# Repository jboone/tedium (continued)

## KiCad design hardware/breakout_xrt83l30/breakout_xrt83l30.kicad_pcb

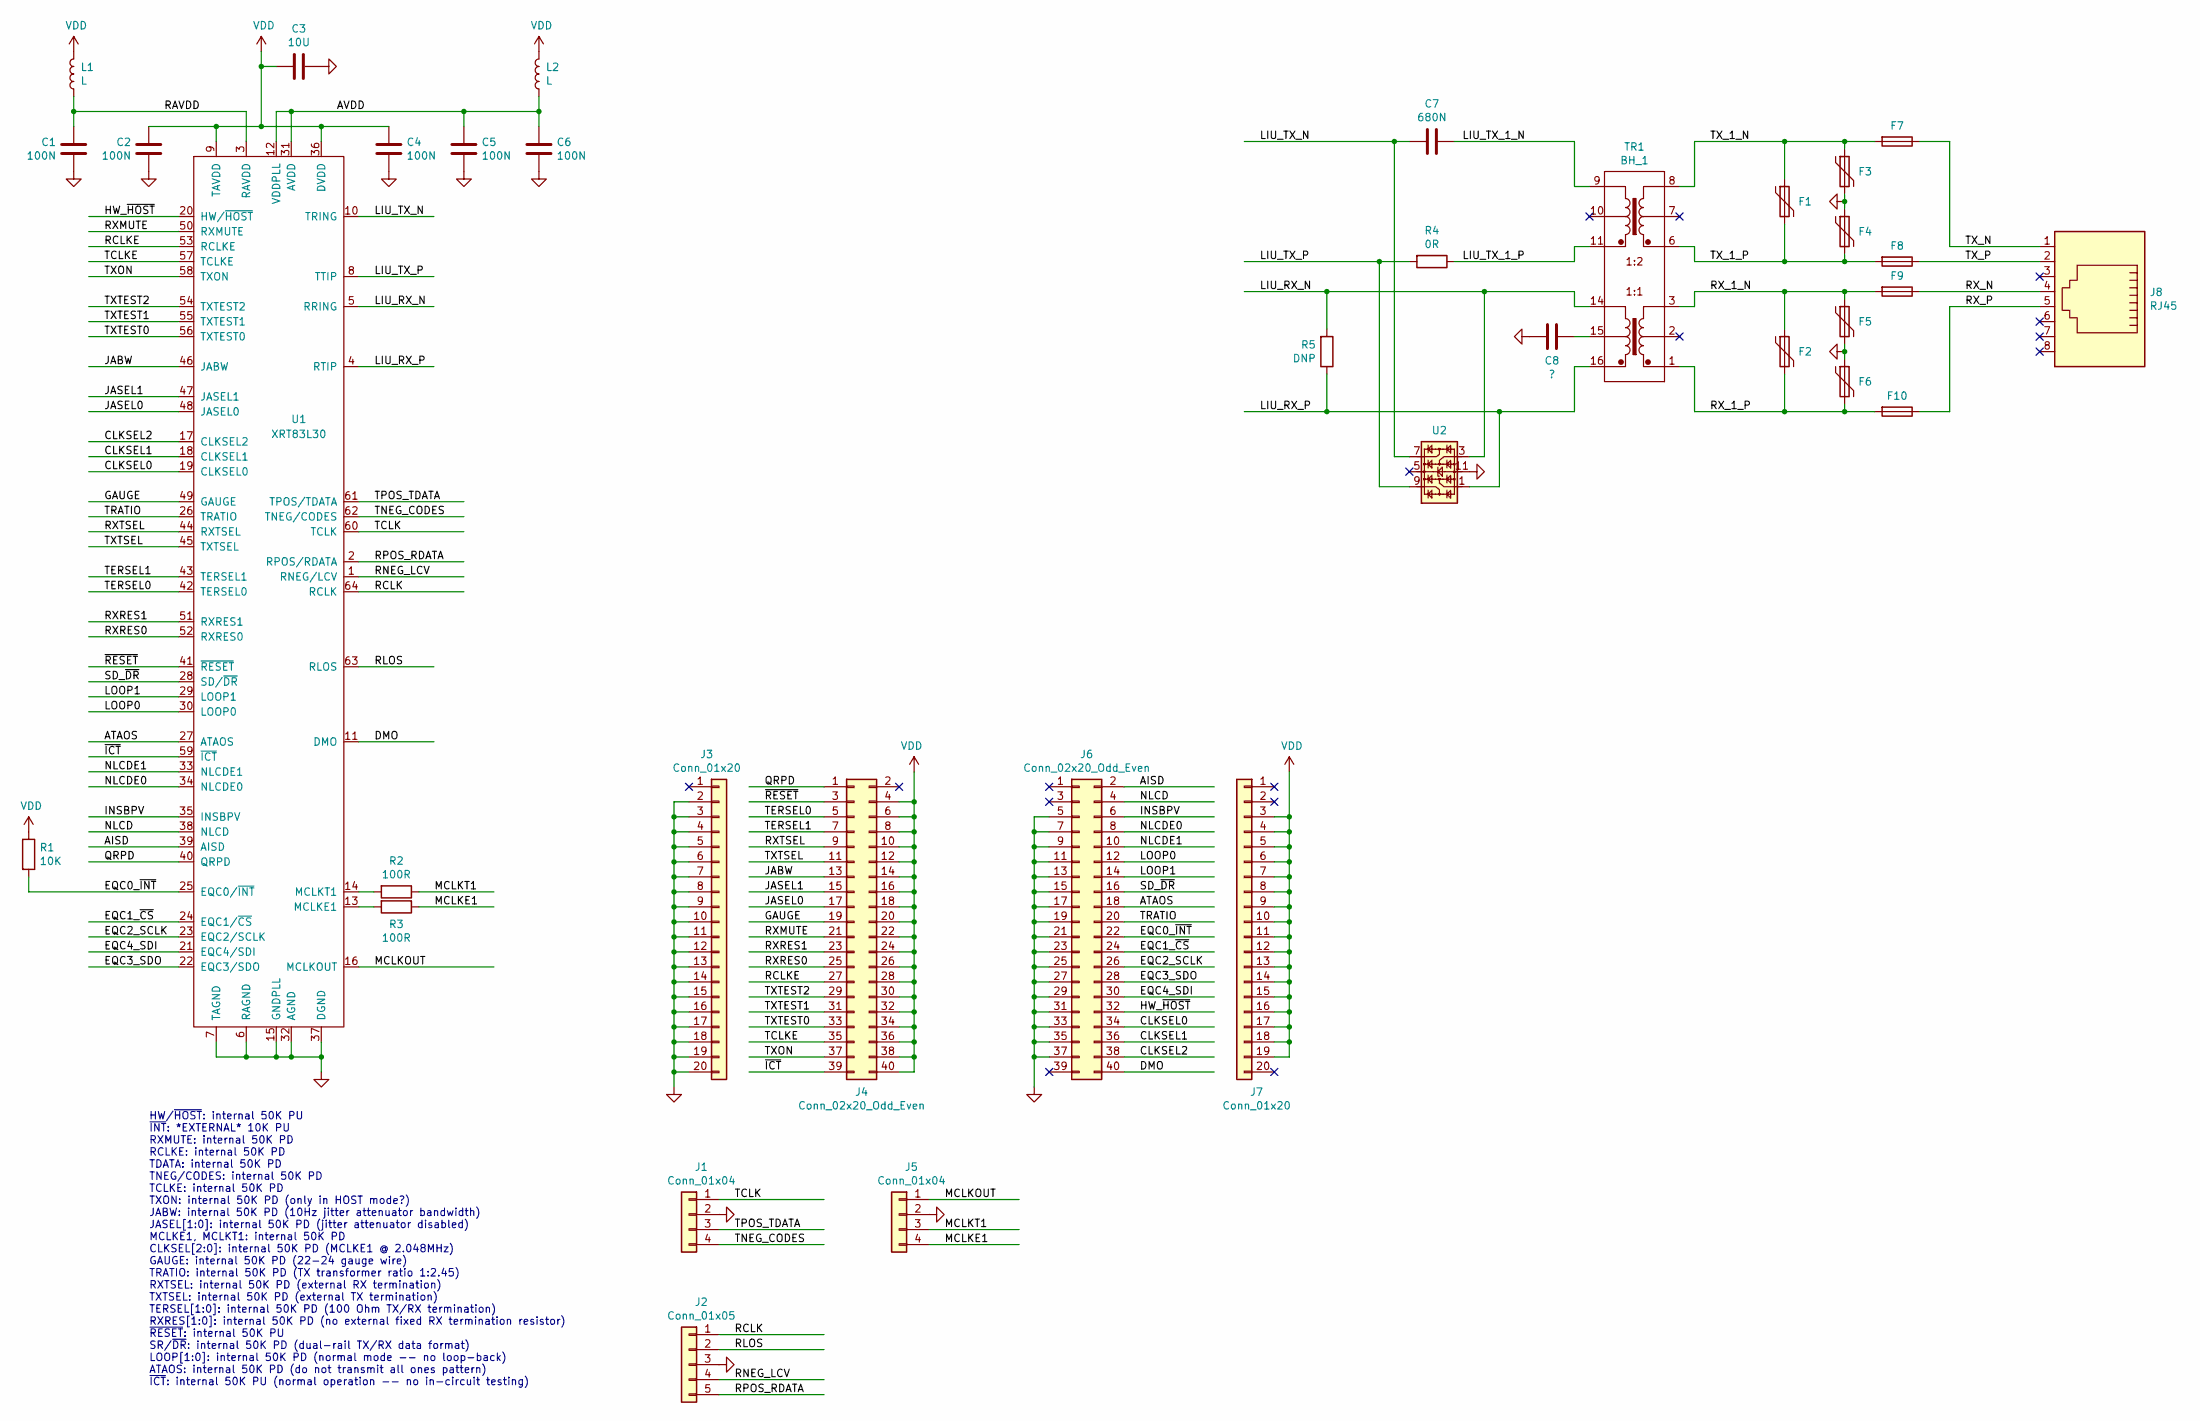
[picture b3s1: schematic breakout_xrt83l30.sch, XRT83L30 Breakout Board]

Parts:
C1, C2, C4, C5, C6: 100N; IPC_CAPC100X50X55L25N
C3: 10U; IPC_CAPC200X125X135L45N
C7: 680N; IPC_CAPC100X50X55L25N
C8: ?; IPC_CAPC200X125X135L45N
F1, F2: Polyfuse; DO-214AA; Part ‎P0080SCMCLRP‎
F3, F4, F5, F6: Polyfuse; DO-214AA; Part ‎P1800SCMCLRP‎
F7, F8, F9, F10: Fuse; 461; Part 04611.25ER
J1, J5: Conn_01x04; PinHeader_1x04_P2.54mm_Vertical
J2: Conn_01x05; PinHeader_1x05_P2.54mm_Vertical
J3, J7: Conn_01x20; PinHeader_1x20_P2.54mm_Vertical
J4, J6: Conn_02x20_Odd_Even; PinHeader_2x20_P2.54mm_Vertical
J8: RJ45; AMPHENOL_RJHSE5080
L1, L2: L; IPC_INDC160X80X100L30N
R1: 10K; IPC_RESC160X80X55L25N
R2, R3: 100R; IPC_RESC160X80X55L25N
R4: 0R; IPC_RESC100X50X40L25N
R5: DNP; IPC_RESC100X50X40L25N
TR1: BH_1; BH; Part T1094NL
U1: XRT83L30; IPC_QFP64P50_1200X1200X160L60X20N
U2: RClamp3304NA; IPC_SON11P50_260X260X65L35X25T215X126N; Part RClamp3304NA

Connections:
/AISD: J6.2, U1.39 (AISD)
/ATAOS: J6.18, U1.27 (ATAOS)
/AVDD: C5.2, C6.2, L2.1, U1.12 (VDDPLL), U1.31 (AVDD)
/CLKSEL0: J6.34, U1.19 (CLKSEL0)
/CLKSEL1: J6.36, U1.18 (CLKSEL1)
/CLKSEL2: J6.38, U1.17 (CLKSEL2)
/DMO: J6.40, U1.11 (DMO)
/EQC0_~INT: J6.22, R1.2, U1.25 (EQC0/~INT)
/EQC1_~CS: J6.24, U1.24 (EQC1/~CS)
/EQC2_SCLK: J6.26, U1.23 (EQC2/SCLK)
/EQC3_SDO: J6.28, U1.22 (EQC3/SDO)
/EQC4_SDI: J6.30, U1.21 (EQC4/SDI)
/GAUGE: J4.19, U1.49 (GAUGE)
/HW_~HOST: J6.32, U1.20 (HW/~HOST)
/INSBPV: J6.6, U1.35 (INSBPV)
/JABW: J4.13, U1.46 (JABW)
/JASEL0: J4.17, U1.48 (JASEL0)
/JASEL1: J4.15, U1.47 (JASEL1)
/LIU_RX_N: R5.2, TR1.14, U1.5 (RRING), U2.3
/LIU_RX_P: R5.1, TR1.16, U1.4 (RTIP), U2.1
/LIU_TX_1_N: C7.1, TR1.9
/LIU_TX_1_P: R4.1, TR1.11
/LIU_TX_N: C7.2, U1.10 (TRING), U2.7
/LIU_TX_P: R4.2, U1.8 (TTIP), U2.9
/LOOP0: J6.12, U1.30 (LOOP0)
/LOOP1: J6.14, U1.29 (LOOP1)
/MCLKE1: J5.4, R3.1
/MCLKOUT: J5.1, U1.16 (MCLKOUT)
/MCLKT1: J5.3, R2.1
/NLCD: J6.4, U1.38 (NLCD)
/NLCDE0: J6.8, U1.34 (NLCDE0)
/NLCDE1: J6.10, U1.33 (NLCDE1)
/QRPD: J4.1, U1.40 (QRPD)
/RAVDD: C1.2, L1.1, U1.3 (RAVDD)
/RCLK: J2.1, U1.64 (RCLK)
/RCLKE: J4.27, U1.53 (RCLKE)
/RLOS: J2.2, U1.63 (RLOS)
/RNEG_LCV: J2.4, U1.1 (RNEG/LCV)
/RPOS_RDATA: J2.5, U1.2 (RPOS/RDATA)
/RXMUTE: J4.21, U1.50 (RXMUTE)
/RXRES0: J4.25, U1.52 (RXRES0)
/RXRES1: J4.23, U1.51 (RXRES1)
/RXTSEL: J4.9, U1.44 (RXTSEL)
/RX_1_N: F2.1, F5.1, F9.2, TR1.3
/RX_1_P: F2.2, F6.2, F10.2, TR1.1
/RX_N: F9.1, J8.4
/RX_P: F10.1, J8.5
/SD_~DR: J6.16, U1.28 (SD/~DR)
/TCLK: J1.1, U1.60 (TCLK)
/TCLKE: J4.35, U1.57 (TCLKE)
/TERSEL0: J4.5, U1.42 (TERSEL0)
/TERSEL1: J4.7, U1.43 (TERSEL1)
/TNEG_CODES: J1.4, U1.62 (TNEG/CODES)
/TPOS_TDATA: J1.3, U1.61 (TPOS/TDATA)
/TRATIO: J6.20, U1.26 (TRATIO)
/TXON: J4.37, U1.58 (TXON)
/TXTEST0: J4.33, U1.56 (TXTEST0)
/TXTEST1: J4.31, U1.55 (TXTEST1)
/TXTEST2: J4.29, U1.54 (TXTEST2)
/TXTSEL: J4.11, U1.45 (TXTSEL)
/TX_1_N: F1.1, F3.1, F7.2, TR1.8
/TX_1_P: F1.2, F4.2, F8.2, TR1.6
/TX_N: F7.1, J8.1
/TX_P: F8.1, J8.2
/~ICT: J4.39, U1.59 (~ICT)
/~RESET: J4.3, U1.41 (~RESET)
GND: C1.1, C2.1, C3.2, C4.1, C5.1, C6.1, C8.2, F3.2, F4.1, F5.2, F6.1, J1.2, J2.3, J3.2, J3.3, J3.4, J3.5, J3.6, J3.7, J3.8, J3.9, J3.10, J3.11, J3.12, J3.13, J3.14, J3.15, J3.16, J3.17, J3.18, J3.19, J3.20, J5.2, J6.5, J6.7, J6.9, J6.11, J6.13, J6.15, J6.17, J6.19, J6.21, J6.23, J6.25, J6.27, J6.29, J6.31, J6.33, J6.35, J6.37, U1.6 (RAGND), U1.7 (TAGND), U1.15 (GNDPLL), U1.32 (AGND), U1.37 (DGND), U2.11
unnamed: C8.1, TR1.15
unnamed: R2.2, U1.14 (MCLKT1)
unnamed: R3.2, U1.13 (MCLKE1)
VDD: C2.2, C3.1, C4.2, J4.4, J4.6, J4.8, J4.10, J4.12, J4.14, J4.16, J4.18, J4.20, J4.22, J4.24, J4.26, J4.28, J4.30, J4.32, J4.34, J4.36, J4.38, J4.40, J7.3, J7.4, J7.5, J7.6, J7.7, J7.8, J7.9, J7.10, J7.11, J7.12, J7.13, J7.14, J7.15, J7.16, J7.17, J7.18, J7.19, L1.2, L2.2, R1.1, U1.9 (TAVDD), U1.36 (DVDD)

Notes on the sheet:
HW/~HOST~: internal 50K PU ~INT~: *EXTERNAL* 10K PU RXMUTE: internal 50K PD RCLKE: internal 50K PD TDATA: internal 50K PD TNEG/CODES: internal 50K PD TCLKE: internal 50K PD TXON: internal 50K PD (only in HOST mode?) JABW: internal 50K PD (10Hz jitter attenuator bandwidth) JASEL[1:0]: internal 50K P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

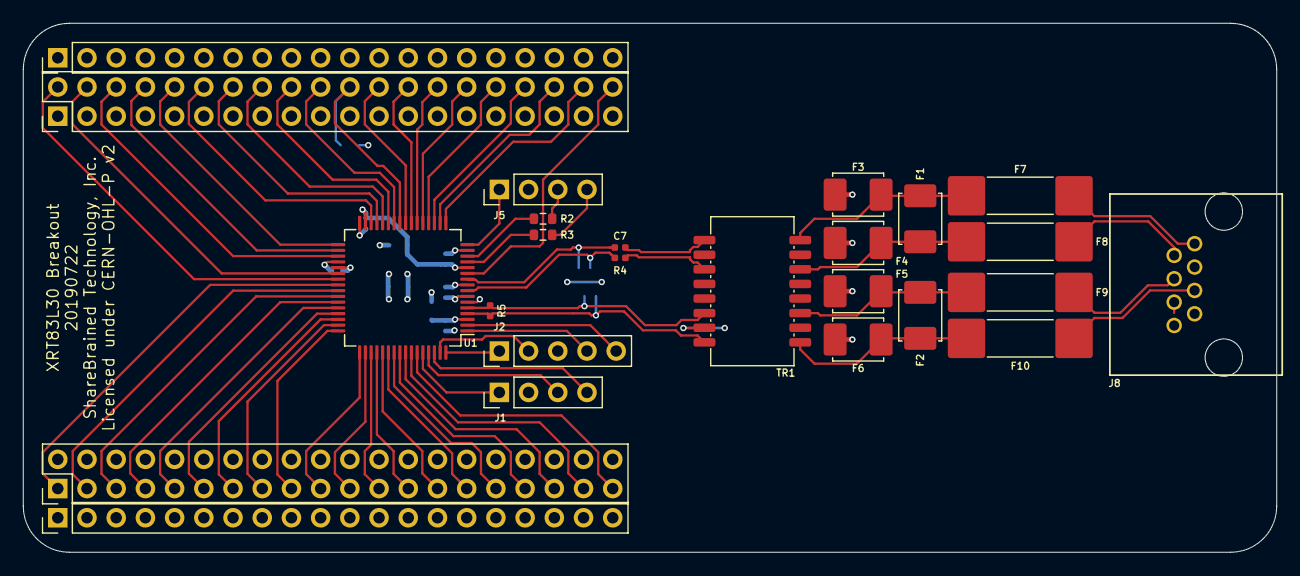
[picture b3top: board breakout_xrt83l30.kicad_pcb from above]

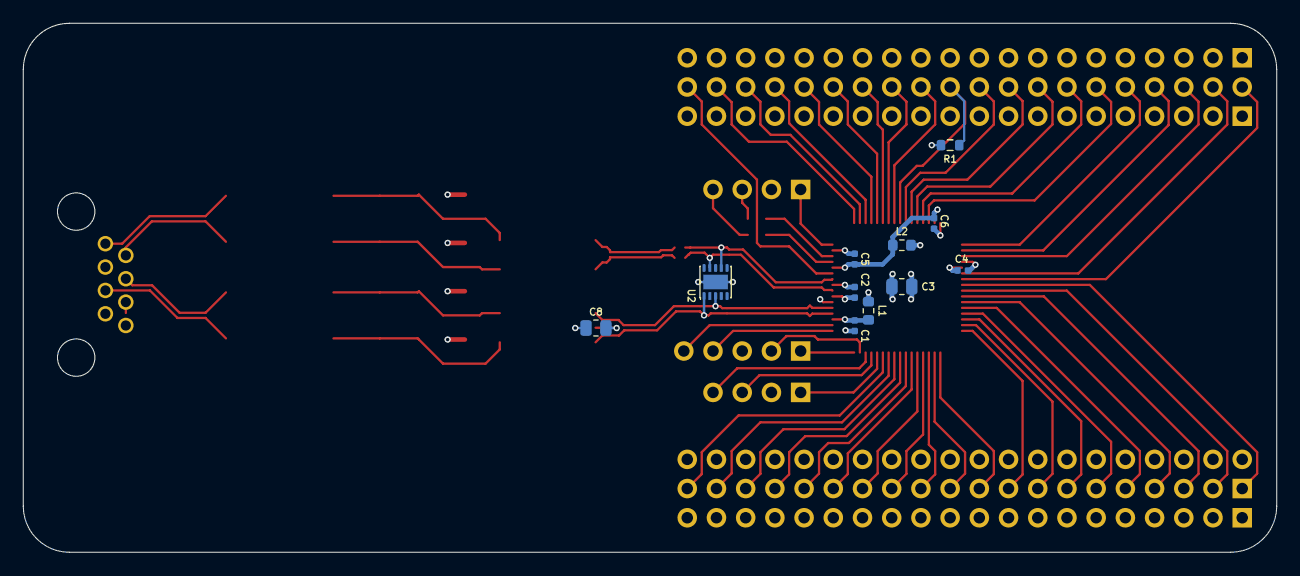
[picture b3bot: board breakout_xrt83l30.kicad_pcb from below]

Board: 4 copper layers, 109.0 x 46.0 mm, 36 parts (11 on the bottom side), 71 nets.

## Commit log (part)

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2019-07-23 Hopefully complete XRT83L30 breakout design.
2019-08-16 Add license, for source code at least.
2019-08-16 Quick dumb Rust test to parse a file of ESF-structured bits. Not terribly useful yet...
2019-08-16 Rust: Save file of 24 channels of raw audio data.
2020-05-29 Relocate XRT83L30 breakout schematic/PCB files.
2020-05-30 Update/apply XRT83L30 breakout schematic license and release dates.
2020-05-30 Add XRT83L30 breakout schematic for reference by non-KiCAD people.
2020-05-30 Add XRT83L30 configuration and bring-up doc.
2020-05-30 Add license for hardware: CERN OHL v2 Permissive
2020-05-30 Update name of project in README.
2020-05-30 Update license info in README.
2020-05-30 Update XRT83L30 breakout schematic -cache.lib because... why?
2020-05-30 Add Tedium X8 (8-span framer/LIU + FPGA + USB + power) schematic/PCB design.
2020-05-30 Remove redundant cached library for XRT83L30 breakout board.
2021-09-01 HW: Tedium X8: Misc schematic comments.
2021-09-01 HW: Tedium X8: Add KiCAD 5.99 project file.
2021-09-01 Rework Rust framer to support ESF.
2021-09-01 Tedium X8 PHY initial design.
    Weak, but it does the job.
2021-09-01 HW: Tedium X8: Add .kicad_prl file
    I guess they separated out UI state from the rest of the project file? Maybe this doesn't belong in the repo?
2021-09-01 HW: Tedium X8: Remove old-KiCAD .pro file.
2021-09-01 Add my KiCAD repo as a submodule.
    I don't like this approach very much, but not sure what's better...
2021-09-01 HW: Tedium X8: Update symbols, footprints, KiCAD to 5.99-now.
2021-09-01 Relicense using BSD 3-Clause.
    Apache and MIT seems complex. Yeah, Rust does it that way. But that doesn't mean I have to.
2021-09-01 Add LUNA-based gateware and tooling/tools.
2021-09-02 Update license on old Rust framer code.
2021-09-19 Reorganize USB endpoint constants
    Borrowing structure from a USB audio device.
2021-09-19 More notes on setup and debugging.
2021-09-19 Further USB descriptor tweaking.
    Set self-powered, 100mA current, remove serial number, add device version number.
2022-06-21 New Rust tedium-tool.
2022-06-21 Remove old Rust framer code.
2022-06-21 Isochronous USB tests in C.
2022-06-21 Some Python ESF frame dumper I cobbled together...
2022-06-21 Clean up Python module imports and directory structure.
2022-06-21 Push forked dependencies to GitHub, point pyproject at them.
2022-06-21 Update top-level README, reflecting significant changes in project.
2022-06-21 Whoops, enable TX side of FPGA framer.
2022-06-21 Fix endpoint numbering on host side.
2022-06-21 Add TX-side structures, and logic to set OUT packet sizes.
2022-06-21 Remove extraneous comment, extra whitespace.
2022-06-22 Remove old, commented-out dependencies.
2022-06-22 Remove message channel, track USB/frame sequences, move frames through ringbuf.
2022-06-22 Drain frame ringbuf as fast as possible.
2022-06-22 Naively pass received frame count to transmitted frame.
    Eventually, I intend for the FPGA to use the frame count as a presentation timestamp, and the host will advance the received count by a constant latency (number of frames). This should make latency m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
2022-06-22 Add simple (and not-so-great) closed-loop TX FIFO management.
2022-06-22 Rename some USB transaction/packet count constants.
2022-06-22 Separate IN/OUT handlers from callback traits.
    First step of larger refactoring.
2022-06-22 Rename internal frames ringbuf producer/consumer.
2022-06-22 Extract the RX packet processing into separate entities.
    Separation of concerns, yay! Keep the gnarly and unsafe USB code contained!
2022-06-22 First pass: collect and report framer statistics.
2022-06-22 Separate periodic and cumulative framer statistics.
2022-06-22 Remove a bunch of old code.
2022-06-22 Loop (poorly-named) processor into audio loop.
2022-06-22 Rename the thing that does the audio processing.
2022-06-22 Quick cut at altering the audio/switch patching at runtime.
2022-06-22 Use thread::Builder to give threads names for better debugging.
2022-06-23 Relocate Microprocessor interface test to tests/hdl.
2022-06-23 Remove some dead/commented code
2022-06-23 Move USB<->microprocessor handler into separate file.
2022-06-23 Reintroduce USB interrupt endpoint for framer INT#.
2022-06-23 Remove more dead code.
2022-06-23 Remove crusty old USB isochronous test program.
2022-06-23 Move USB config info into module, fix interrupt endpoint number.
2022-06-24 Add USB interrupt IN endpoint simulation.
2022-06-24 Move framer->USB interrupt logic out of endpoint code.
2022-06-24 "Fix" framer->USB interrupts, at least temporariliy.
    TODO: This method certainly transmits far more interrupts than necessary, and likely wastes some small (likely insignificant) amount of the host's time. I suppose it offends me aesthetically more tha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
2022-06-24 Missed committing sneaky comment about RTKit thread priority.
2022-06-25 Add common reset signal for PLLs, currently held at 0/false.
2022-06-25 Remove clkref domain.
2022-06-25 Add FTDI-attached UARTResource.
2022-06-25 Fix platform default clock frequencies.
2022-06-25 Clean up clock signal resets.
2022-06-25 Move MCLKIN assignment to clock domain generator.
2022-06-25 Clean up whitespace, remove commented code.
2022-06-26 Cargo-culting little tweak to ensure reference clock is an input.
2022-06-26 Revert "Simplify and speed up microprocessor interface."
    This reverts commit f15058377d9bab2b0ec8e4d6040b9b5df1753b87.
2022-06-26 Add MicroprocessorInterface `done` strobe signal.
2022-06-28 Extract microprocessor bus wait-state into constant.
2022-06-28 Add firmware Rust code and semi-generalized framer peripheral crate.
2022-06-28 Add typing to top module `platform` for code completion.
2022-06-28 Change building of top-level module to support SoC.
2022-06-28 Whoops, add platform to usb_framer elaboration function.
2022-06-28 Introduce SoC, move framer hardware reset control to SoC CSR.
2022-06-28 Half-heartedly update READMEs.
2022-06-28 openocd: Remove redundant selection of JTAG transport mode.
2022-06-28 Break nascent firmware into several source files.
2022-06-28 Note about how to reload the FPGA without rebuilding the bitstream.
2022-06-28 Add some useful bits to the dumb UART.
    Trying not to be embarrassed.
2022-06-28 firmware: basic interrupt checking.
2022-06-28 Bump linker RAM size to 16K to match earlier gateware change.
2022-06-28 Enable debouncing of RBS state on all timeslots.
2022-06-28 Add a couple of firmware start-up progress messages.
2022-06-28 Allow comparisons of RSAR registers.
2022-06-28 Quick and dirty monitoring of per-timeslot RBS state.
2022-06-29 More thorough clearing of HDLC/SS7-related interrupts.
2022-06-29 Firmware: Report interrupt status to host over USB IN endpoint.
2022-06-29 Typo/comment clean-up.
2022-06-29 firmware: Accept USB OUT transfers.
    They're just being printed via the UART right now, but we'll do something more interesting with them soon...
2022-06-29 Prevent firmware from being built at workspace level.
    Doing so would ignore the firmware project's .cargo configuration, which is critical for getting the correct binary.
2022-06-29 firmware: Optimize for size.
2022-06-29 Remove a couple of bits of commented-out code.
2022-06-29 firmware: Break USB, Peripheral into separate files.
2022-06-29 Remove init code from host side, now the firmware does it.
2022-06-29 firmware: Change resync feature to have trigger boolean.
    Eventually, the host will be able to trigger a resync.
2022-06-29 Move IsochronousTransfer to usb module.
    It'll get generalized soon...
2022-06-29 Rename USB transfer callback.
2022-06-29 Generalize async USB transfer handler, improve framer interrupt thread..
2022-06-29 firmware: Only arm interrupt IN when there's data in the FIFO.
    This prevents a ton of zero-length packets (ZLPs) being sent to the host and waking it up unnecessarily.
2022-06-29 Pipe framer interrupt data through to receiver thread.
2022-06-29 Oh look, more host code that was moved to the SoC.
2022-06-29 firmware: Restore unhandled BISR events and comments for each event type.
2022-06-29 firmware: Send correct RLCISRx registers for LBCODE, fix PAC crate.
2022-06-29 firmware: Send entire RDLBC register, not just byte count.
2022-06-29 Firmware: rename timeslot RBS nibbles for clarity.
2022-06-29 Firmware: Always report HDLC length, read bytes, if DLSR is not zero.
2022-06-29 Firmware: Report SS7SRx.
2022-06-29 Parse and pretty-print framer interrupt messages.
    This needs to be refactored into separate parsing and presentation, obviously...
2022-06-30 Proper parsing and displaying of framer interrupts.
2022-06-30 Move framer register dump functions, remove commented code.
2022-06-30 Put a copy of USB descriptor constants in firmware.
2022-06-30 Add some missing USB descriptor constants.
2022-06-30 Separate host command parsing from processing.
2022-06-30 Change Python host command test to do a register read.
2022-06-30 Move OUT endpoint check outside of command parser.
2022-07-01 Remove `owner` register from USB OUT endpoint.
2022-07-01 Do some SoC USB variable renaming.
2022-07-01 Firmware: Move USB IN interrupt checking to later to not starve host requests.
2022-07-01 Remove commented code.
2022-07-01 Add USB IN endpoint for host commands.
2022-07-01 Firmware: USB OUT: check `enable` first for endpoint transaction completion.
2022-07-01 Firmware: USB IN: Add `is_stalled` function.
2022-07-01 Test: Host Request: separate read and write exceptions, run as fast as possible.
2022-07-01 Test: Make host command test quieter, faster, for max damage.
2022-07-01 Firmware: Tighten up RegisterRead, monitor for unexpected USB IN state.
2022-07-01 Firmware: Add register-write host command.
2022-07-01 Test: Rewrite host command test, more tidy, with multiple tests.
2022-07-01 Firmware: Add UART test code.
    I might never use it again, but who knows...
2022-07-01 Test: Rename Python USB interrupt/host-command tests.
2022-07-01 Test: Fix the ringer host command test to use correct A/B bits for loop-start.
2022-07-01 Tool: Make a bunch of types and fields public.
2022-07-01 Tool: Move test patch controller to main.rs.
2022-07-01 Tool: Track received line state.
2022-07-10 Add Arch udev rules, rename Debian udev rules.
2022-07-10 soc: README.md tweaks.
2022-07-10 hdl: README.md tweaks.
2022-07-10 tedium-tool: Remove dead code.
2022-07-10 Rust: Clean up a bunch of warnings, comment some things.
2022-07-10 Remove framer defaults from tedium-tool, will use xrt86vx38-pac soon.
2022-07-10 xrt86vx38-pac: Adjust global defaults to read a read-to-clear register.
2022-07-10 tedium-tool: Move framer interrupt handling to interrupt.rs.
2022-07-10 framer: Rework the interrupt handler a bit.
    Order of operations was less than ideal. We need to copy out of the libusb transfer buffer before we submit the transfer back to libusb.
2022-07-10 tedium-tool: Change placement of carriage returns in debug output.
2022-07-10 tedium-tool: Track line state and time-stamp hook-switch events.
    Pulse dialing is essential!
2022-07-10 tedium-tool: Silence structure-structuring warning for unused field.
2022-07-10 tedium-tool: Move debug thread out of audio.rs, to main.rs:monitor.
2022-07-11 Add MF bits to RX frame, move signaling (DTMF/pulse) into separate thread.
    Don't burden the audio thread with DTMF processing, as a little latency will be totally acceptable. I'll eventually add hook-switch detection (pulse dialing, flash, on-hook events) based on RBS bits 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
2022-07-11 tedium-tool: print an error when the signaling ring buffer overflows.
2022-07-11 tedium-tool: Expand signaling ring buffer, increase sleep time.
2022-07-11 tedium-tool: Collect RBS signaling.
2022-07-11 tedium-tool: Extract missing-frames detector.
2022-07-11 tedium-tool: Make audio debug messages easily switchable.
2022-07-11 tedium-tool: Code to collect ESF superframe bits.
    Not sure if I'll ever use it, but it's there, making the Rust compiler spit warnings at me.
2022-07-11 tedium-tool: Extract RBS state tracking.
